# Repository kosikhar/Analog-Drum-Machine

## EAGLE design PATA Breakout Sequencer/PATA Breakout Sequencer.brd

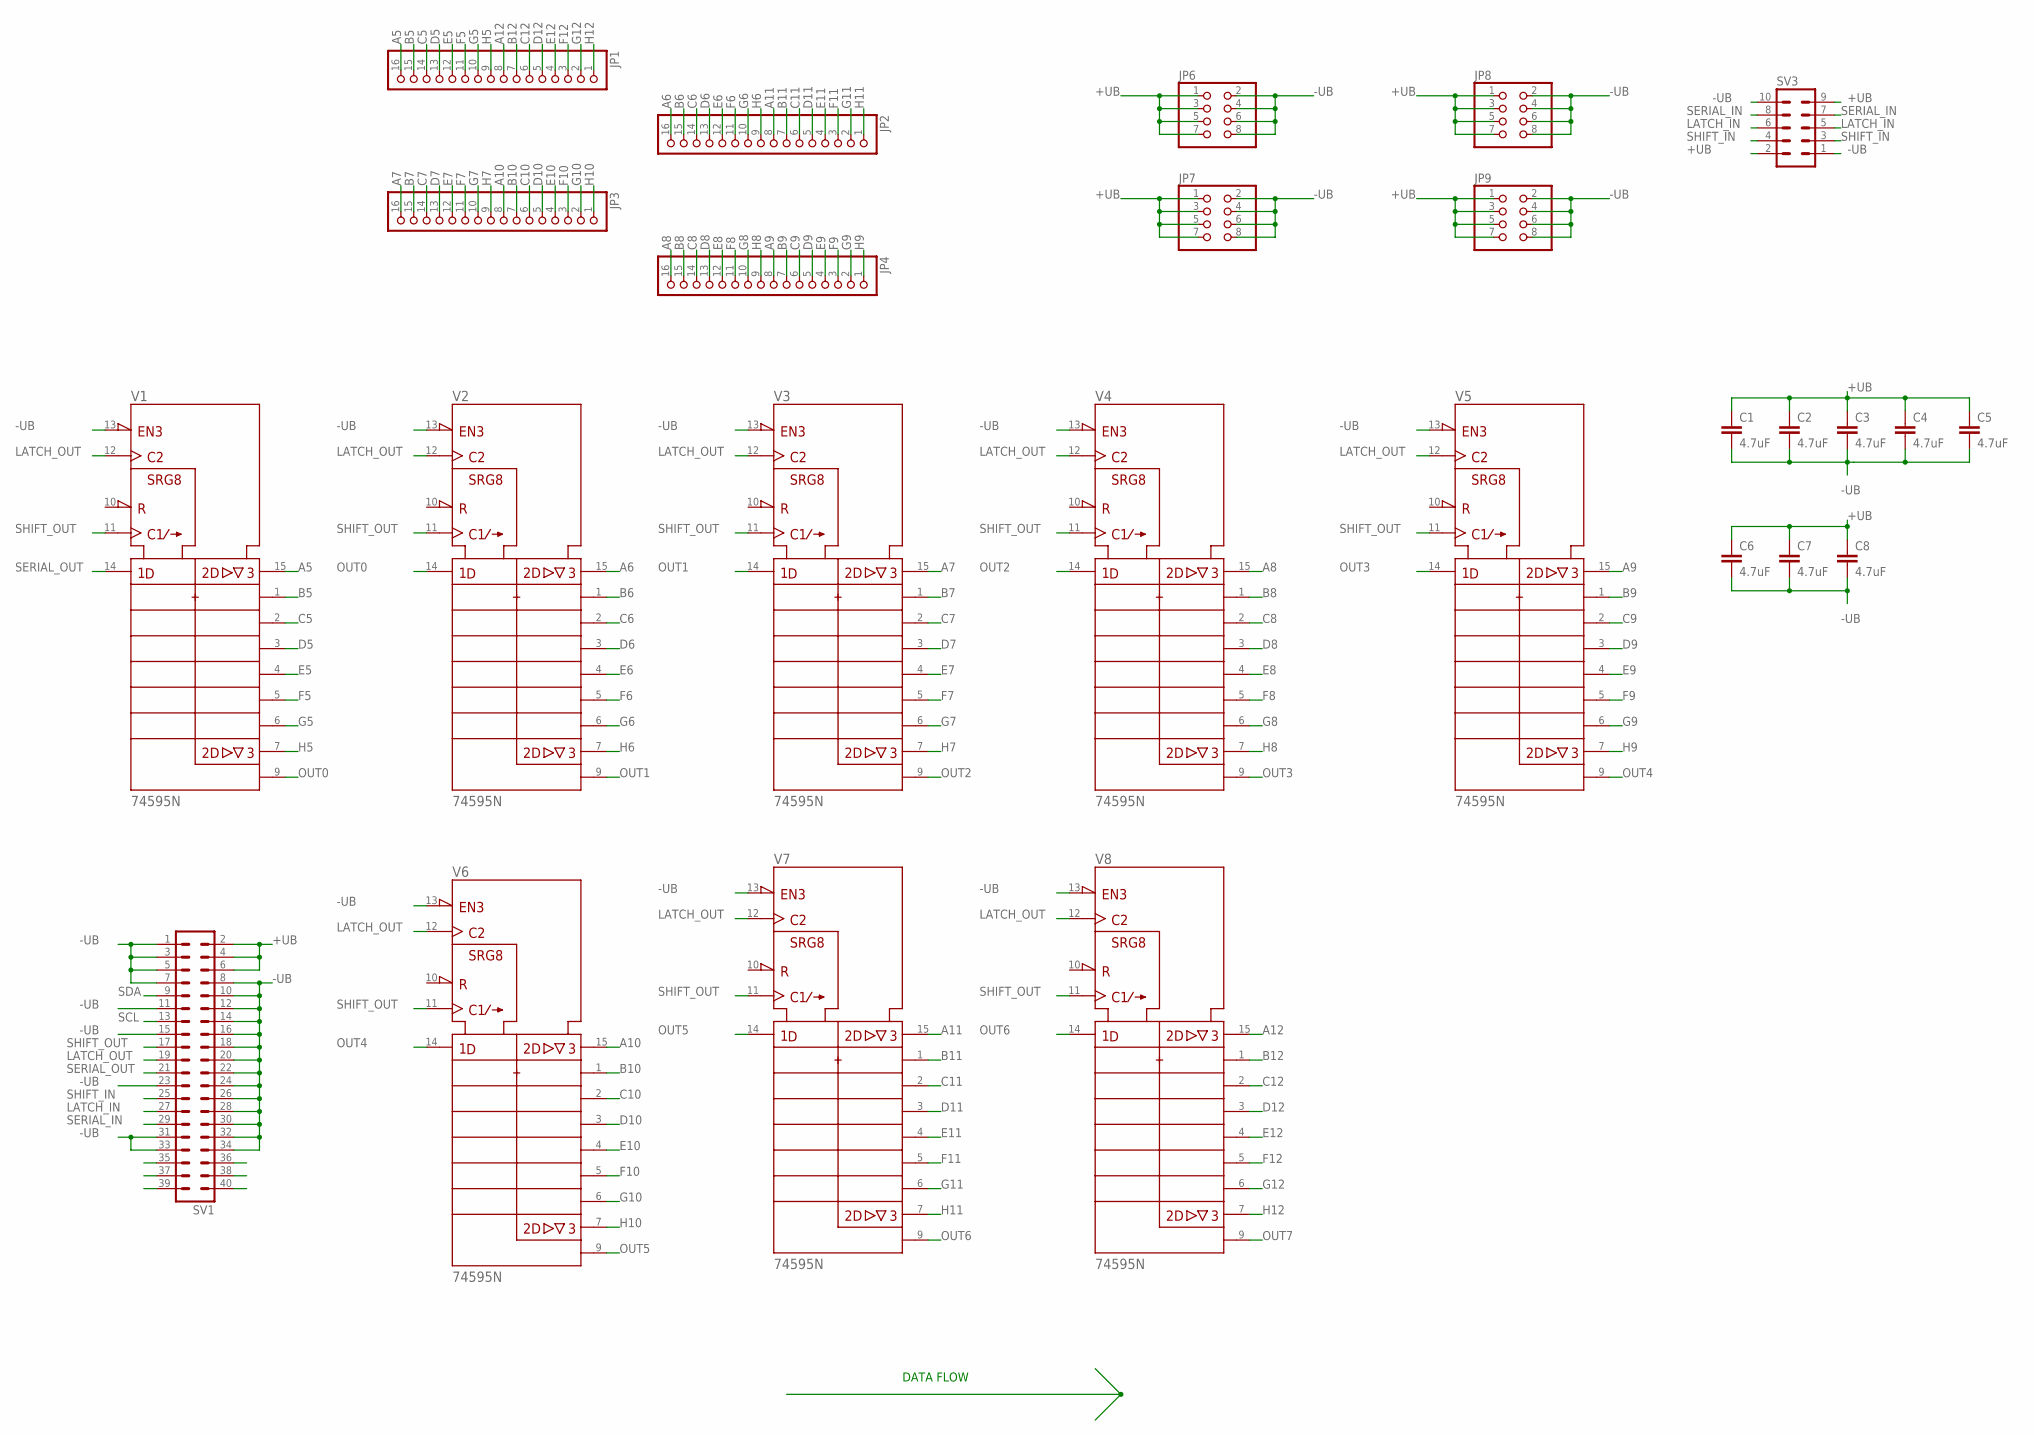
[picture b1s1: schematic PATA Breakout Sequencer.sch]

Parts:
C1, C2, C3, C4, C5, C6, C7, C8: 4.7uF; C050-024X044
JP1, JP2, JP3, JP4: PINHD-1X16; 1X16
JP6, JP7, JP8, JP9: PINHD-2X4; 2X04
SV1: MA20-2
SV3: MA05-2
V1, V2, V3, V4, V5, V6, V7, V8: 74595N; DIL16

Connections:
+UB: C1.1, C2.1, C3.1, C4.1, C5.1, C6.1, C7.1, C8.1, JP6.1, JP6.3, JP6.5, JP6.7, JP7.1, JP7.3, JP7.5, JP7.7, JP8.1, JP8.3, JP8.5, JP8.7, JP9.1, JP9.3, JP9.5, JP9.7, SV1.2, SV1.4, SV1.6, SV3.2, SV3.9, V1.16 (+UB), V2.16 (+UB), V3.16 (+UB), V4.16 (+UB), V5.16 (+UB), V6.16 (+UB), V7.16 (+UB), V8.16 (+UB)
-UB: C1.2, C2.2, C3.2, C4.2, C5.2, C6.2, C7.2, C8.2, JP6.2, JP6.4, JP6.6, JP6.8, JP7.2, JP7.4, JP7.6, JP7.8, JP8.2, JP8.4, JP8.6, JP8.8, JP9.2, JP9.4, JP9.6, JP9.8, SV1.1, SV1.3, SV1.5, SV1.7, SV1.8, SV1.10, SV1.11, SV1.12, SV1.14, SV1.15, SV1.16, SV1.18, SV1.20, SV1.22, SV1.23, SV1.24, SV1.26, SV1.28, SV1.30, SV1.31, SV1.32, SV1.33, SV1.34, SV3.1, SV3.10, V1.8 (-UB), V1.13 (!G), V2.8 (-UB), V2.13 (!G), V3.8 (-UB), V3.13 (!G), V4.8 (-UB), V4.13 (!G), V5.8 (-UB), V5.13 (!G), V6.8 (-UB), V6.13 (!G), V7.8 (-UB), V7.13 (!G), V8.8 (-UB), V8.13 (!G)
A5: JP1.16, V1.15 (QA)
A6: JP2.16, V2.15 (QA)
A7: JP3.16, V3.15 (QA)
A8: JP4.16, V4.15 (QA)
A9: JP4.8, V5.15 (QA)
A10: JP3.8, V6.15 (QA)
A11: JP2.8, V7.15 (QA)
A12: JP1.8, V8.15 (QA)
B5: JP1.15, V1.1 (QB)
B6: JP2.15, V2.1 (QB)
B7: JP3.15, V3.1 (QB)
B8: JP4.15, V4.1 (QB)
B9: JP4.7, V5.1 (QB)
B10: JP3.7, V6.1 (QB)
B11: JP2.7, V7.1 (QB)
B12: JP1.7, V8.1 (QB)
C5: JP1.14, V1.2 (QC)
C6: JP2.14, V2.2 (QC)
C7: JP3.14, V3.2 (QC)
C8: JP4.14, V4.2 (QC)
C9: JP4.6, V5.2 (QC)
C10: JP3.6, V6.2 (QC)
C11: JP2.6, V7.2 (QC)
C12: JP1.6, V8.2 (QC)
D5: JP1.13, V1.3 (QD)
D6: JP2.13, V2.3 (QD)
D7: JP3.13, V3.3 (QD)
D8: JP4.13, V4.3 (QD)
D9: JP4.5, V5.3 (QD)
D10: JP3.5, V6.3 (QD)
D11: JP2.5, V7.3 (QD)
D12: JP1.5, V8.3 (QD)
E5: JP1.12, V1.4 (QE)
E6: JP2.12, V2.4 (QE)
E7: JP3.12, V3.4 (QE)
E8: JP4.12, V4.4 (QE)
E9: JP4.4, V5.4 (QE)
E10: JP3.4, V6.4 (QE)
E11: JP2.4, V7.4 (QE)
E12: JP1.4, V8.4 (QE)
F5: JP1.11, V1.5 (QF)
F6: JP2.11, V2.5 (QF)
F7: JP3.11, V3.5 (QF)
F8: JP4.11, V4.5 (QF)
F9: JP4.3, V5.5 (QF)
F10: JP3.3, V6.5 (QF)
F11: JP2.3, V7.5 (QF)
F12: JP1.3, V8.5 (QF)
G5: JP1.10, V1.6 (QG)
G6: JP2.10, V2.6 (QG)
G7: JP3.10, V3.6 (QG)
G8: JP4.10, V4.6 (QG)
G9: JP4.2, V5.6 (QG)
G10: JP3.2, V6.6 (QG)
G11: JP2.2, V7.6 (QG)
G12: JP1.2, V8.6 (QG)
H5: JP1.9, V1.7 (QH)
H6: JP2.9, V2.7 (QH)
H7: JP3.9, V3.7 (QH)
H8: JP4.9, V4.7 (QH)
H9: JP4.1, V5.7 (QH)
H10: JP3.1, V6.7 (QH)
H11: JP2.1, V7.7 (QH)
H12: JP1.1, V8.7 (QH)
LATCH_IN: SV1.27, SV3.5, SV3.6
LATCH_OUT: SV1.19, V1.12 (RCK), V2.12 (RCK), V3.12 (RCK), V4.12 (RCK), V5.12 (RCK), V6.12 (RCK), V7.12 (RCK), V8.12 (RCK)
OUT0: V1.9 (QH*), V2.14 (SER)
OUT1: V2.9 (QH*), V3.14 (SER)
OUT2: V3.9 (QH*), V4.14 (SER)
OUT3: V4.9 (QH*), V5.14 (SER)
OUT4: V5.9 (QH*), V6.14 (SER)
OUT5: V6.9 (QH*), V7.14 (SER)
OUT6: V7.9 (QH*), V8.14 (SER)
OUT7: V8.9 (QH*)
SCL: SV1.13
SDA: SV1.9
SERIAL_IN: SV1.29, SV3.7, SV3.8
SERIAL_OUT: SV1.21, V1.14 (SER)
SHIFT_IN: SV1.25, SV3.3, SV3.4
SHIFT_OUT: SV1.17, V1.11 (SRCK), V2.11 (SRCK), V3.11 (SRCK), V4.11 (SRCK), V5.11 (SRCK), V6.11 (SRCK), V7.11 (SRCK), V8.11 (SRCK)

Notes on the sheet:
DATA FLOW

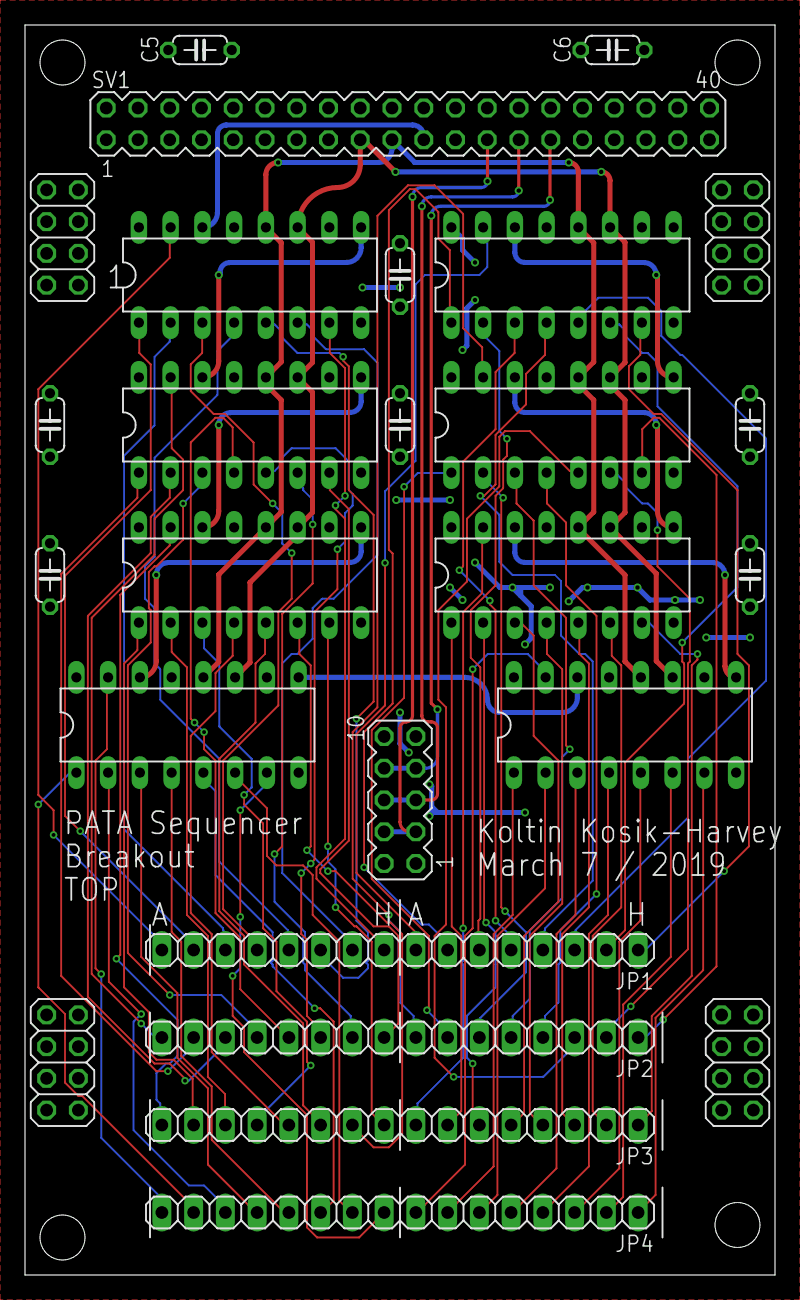
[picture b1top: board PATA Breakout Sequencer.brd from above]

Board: 2 copper layers, 60.0 x 100.0 mm, 26 parts (0 on the bottom side), 79 nets.

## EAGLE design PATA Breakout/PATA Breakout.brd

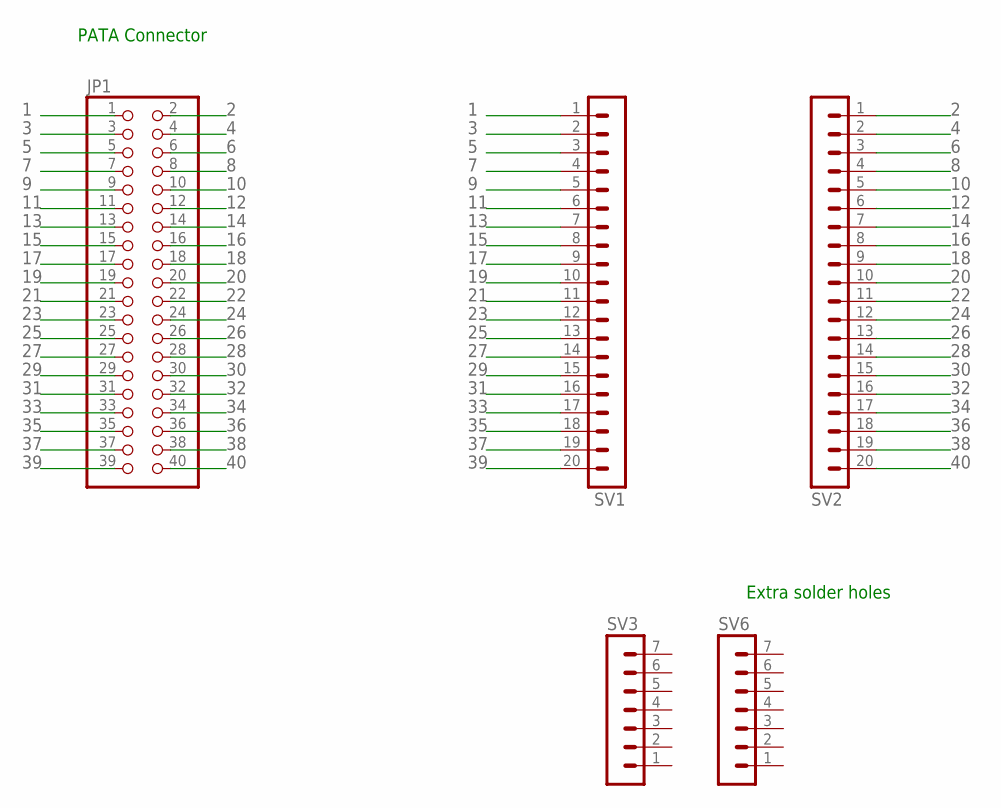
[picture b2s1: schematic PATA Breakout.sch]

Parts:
JP1: PINHD-2X20; 2X20
SV1, SV2: MA20-1L
SV3, SV6: MA07-1

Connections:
1: JP1.1, SV1.1
2: JP1.2, SV2.1
3: JP1.3, SV1.2
4: JP1.4, SV2.2
5: JP1.5, SV1.3
6: JP1.6, SV2.3
7: JP1.7, SV1.4
8: JP1.8, SV2.4
9: JP1.9, SV1.5
10: JP1.10, SV2.5
11: JP1.11, SV1.6
12: JP1.12, SV2.6
13: JP1.13, SV1.7
14: JP1.14, SV2.7
15: JP1.15, SV1.8
16: JP1.16, SV2.8
17: JP1.17, SV1.9
18: JP1.18, SV2.9
19: JP1.19, SV1.10
20: JP1.20, SV2.10
21: JP1.21, SV1.11
22: JP1.22, SV2.11
23: JP1.23, SV1.12
24: JP1.24, SV2.12
25: JP1.25, SV1.13
26: JP1.26, SV2.13
27: JP1.27, SV1.14
28: JP1.28, SV2.14
29: JP1.29, SV1.15
30: JP1.30, SV2.15
31: JP1.31, SV1.16
32: JP1.32, SV2.16
33: JP1.33, SV1.17
34: JP1.34, SV2.17
35: JP1.35, SV1.18
36: JP1.36, SV2.18
37: JP1.37, SV1.19
38: JP1.38, SV2.19
39: JP1.39, SV1.20
40: JP1.40, SV2.20

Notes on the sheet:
PATA Connector
Extra solder holes

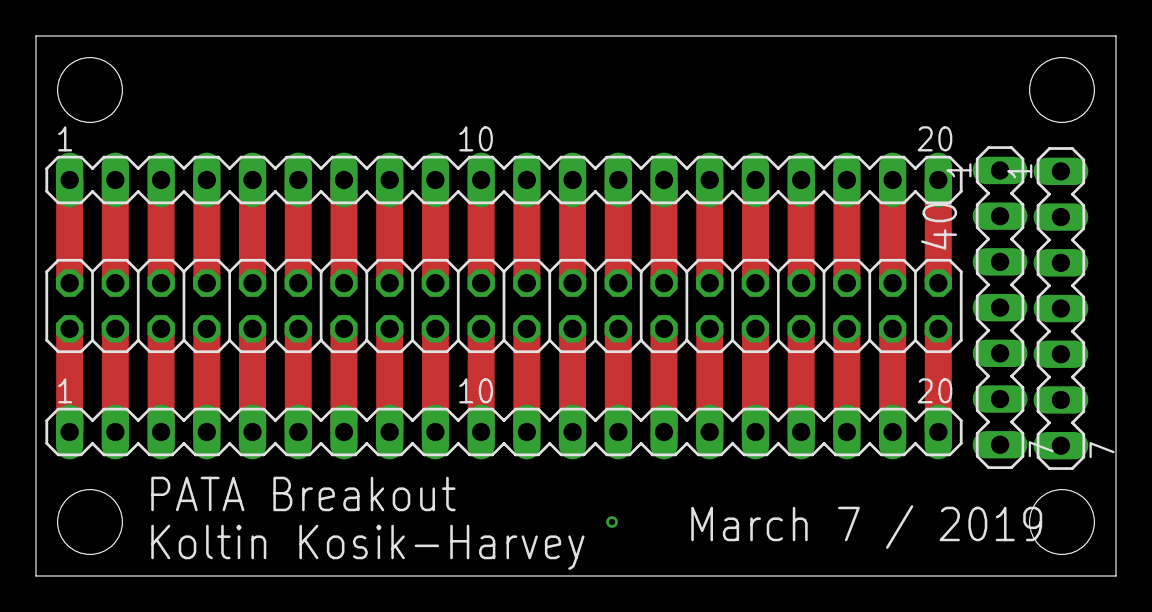
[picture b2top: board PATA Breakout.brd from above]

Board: 2 copper layers, 60.0 x 30.0 mm, 5 parts (0 on the bottom side), 40 nets.

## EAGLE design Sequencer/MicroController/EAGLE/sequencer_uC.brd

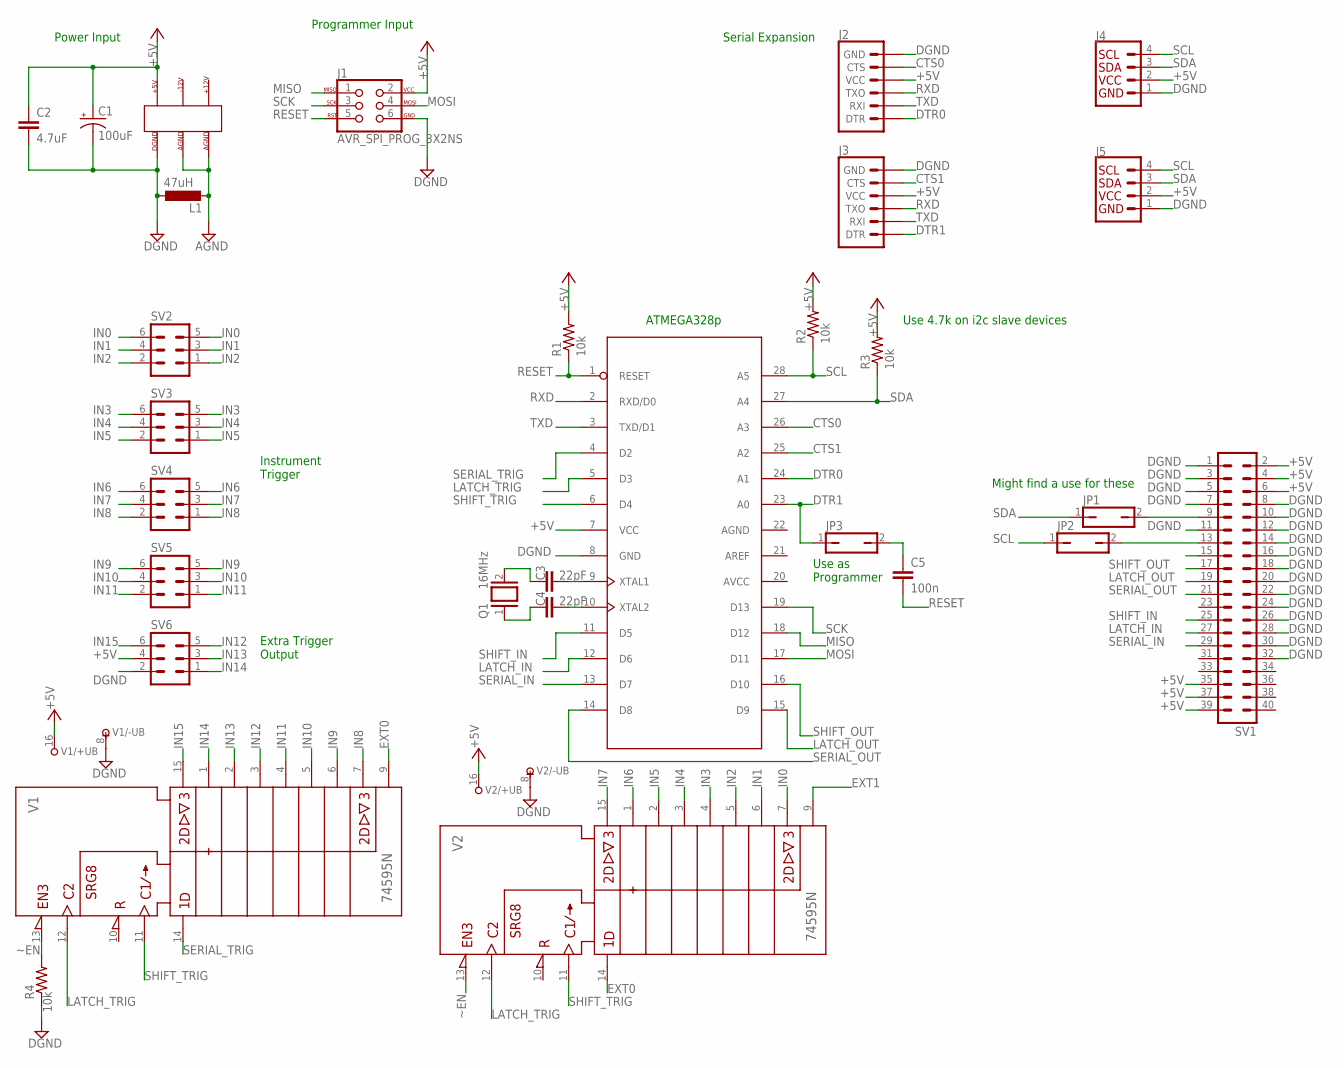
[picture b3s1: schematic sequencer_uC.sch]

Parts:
AT1: ATMEGA328; DIP28-0.3IN
C1: 100uF; E5-8,5
C2: 4.7uF; C050-024X044
C3, C4: 22pF; C050-024X044
C5: 100n; C050-024X044
J1: AVR_SPI_PROG_3X2NS; 2X3-NS
J2, J3: 6_PIN_SERIAL_TARGETLONGPADS; 1X06_LONGPADS
J4, J5: I2C_STANDARD; 1X04
JP1, JP2, JP3: JP1Q; JP1
L1: 47uH; 0207/10
Q1: 16MHz; QS
R1, R2, R3, R4: 10k; 0204/7
SV1: MA20-2
SV2, SV3, SV4, SV5, SV6: MA03-2
U$1: TER6PIN_VERT; CAPSTONE_1-770875-0
V1, V2: 74595N; DIL16

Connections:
+5V: AT1.7 (VCC), C1.+, C2.1, J1.2, J2.4 (VCC), J3.4 (VCC), J4.2, J5.2, R1.2, R2.2, R3.2, SV1.2, SV1.4, SV1.6, SV1.35, SV1.37, SV1.39, SV6.4, U$1.+5V, V1.16 (+UB), V2.16 (+UB)
AGND: L1.2, U$1.AGND0, U$1.AGND1
CTS0: AT1.26 (A3), J2.5 (CTS)
CTS1: AT1.25 (A2), J3.5 (CTS)
DGND: AT1.8 (GND), C1.-, C2.2, J1.6, J2.6 (GND), J3.6 (GND), J4.1, J5.1, L1.1, R4.1, SV1.1, SV1.3, SV1.5, SV1.7, SV1.8, SV1.10, SV1.11, SV1.12, SV1.14, SV1.15, SV1.16, SV1.18, SV1.20, SV1.22, SV1.24, SV1.26, SV1.28, SV1.30, SV1.32, SV6.2, U$1.DGND, U$1.NULL (DGND), V1.8 (-UB), V2.8 (-UB)
DTR0: AT1.24 (A1), J2.1 (DTR)
DTR1: AT1.23 (A0), J3.1 (DTR), JP3.1
EXT0: V1.9 (QH*), V2.14 (SER)
EXT1: V2.9 (QH*)
IN0: SV2.5, SV2.6, V2.7 (QH)
IN1: SV2.3, SV2.4, V2.6 (QG)
IN2: SV2.1, SV2.2, V2.5 (QF)
IN3: SV3.5, SV3.6, V2.4 (QE)
IN4: SV3.3, SV3.4, V2.3 (QD)
IN5: SV3.1, SV3.2, V2.2 (QC)
IN6: SV4.5, SV4.6, V2.1 (QB)
IN7: SV4.3, SV4.4, V2.15 (QA)
IN8: SV4.1, SV4.2, V1.7 (QH)
IN9: SV5.5, SV5.6, V1.6 (QG)
IN10: SV5.3, SV5.4, V1.5 (QF)
IN11: SV5.1, SV5.2, V1.4 (QE)
IN12: SV6.5, V1.3 (QD)
IN13: SV6.3, V1.2 (QC)
IN14: SV6.1, V1.1 (QB)
IN15: SV6.6, V1.15 (QA)
LATCH_IN: AT1.12 (D6), SV1.27
LATCH_OUT: AT1.15 (D9), SV1.19
LATCH_TRIG: AT1.5 (D3), V1.12 (RCK), V2.12 (RCK)
MISO: AT1.18 (D12), J1.1
MOSI: AT1.17 (D11), J1.4
unnamed: AT1.9 (XTAL1), C3.2
unnamed: AT1.10 (XTAL2), C4.2
unnamed: C3.1, Q1.2
unnamed: C4.1, Q1.1
unnamed: JP2.2, SV1.13
unnamed: JP1.2, SV1.9
unnamed: C5.1, JP3.2
RESET: AT1.1 (RESET), C5.2, J1.5, R1.1
RXD: AT1.2 (RXD/D0), J2.3 (TXO), J3.3 (TXO)
SCK: AT1.19 (D13), J1.3
SCL: AT1.28 (A5), J4.4, J5.4, JP2.1, R2.1
SDA: AT1.27 (A4), J4.3, J5.3, JP1.1, R3.1
SERIAL_IN: AT1.13 (D7), SV1.29
SERIAL_OUT: AT1.14 (D8), SV1.21
SERIAL_TRIG: AT1.4 (D2), V1.14 (SER)
SHIFT_IN: AT1.11 (D5), SV1.25
SHIFT_OUT: AT1.16 (D10), SV1.17
SHIFT_TRIG: AT1.6 (D4), V1.11 (SRCK), V2.11 (SRCK)
TXD: AT1.3 (TXD/D1), J2.2 (RXI), J3.2 (RXI)
~EN: R4.2, V1.13 (!G), V2.13 (!G)

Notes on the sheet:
ATMEGA328p
Serial Expansion
Power Input
Programmer Input
Instrument Trigger
Extra Trigger Output
Use 4.7k on i2c slave devices
Might find a use for these
Use as Programmer

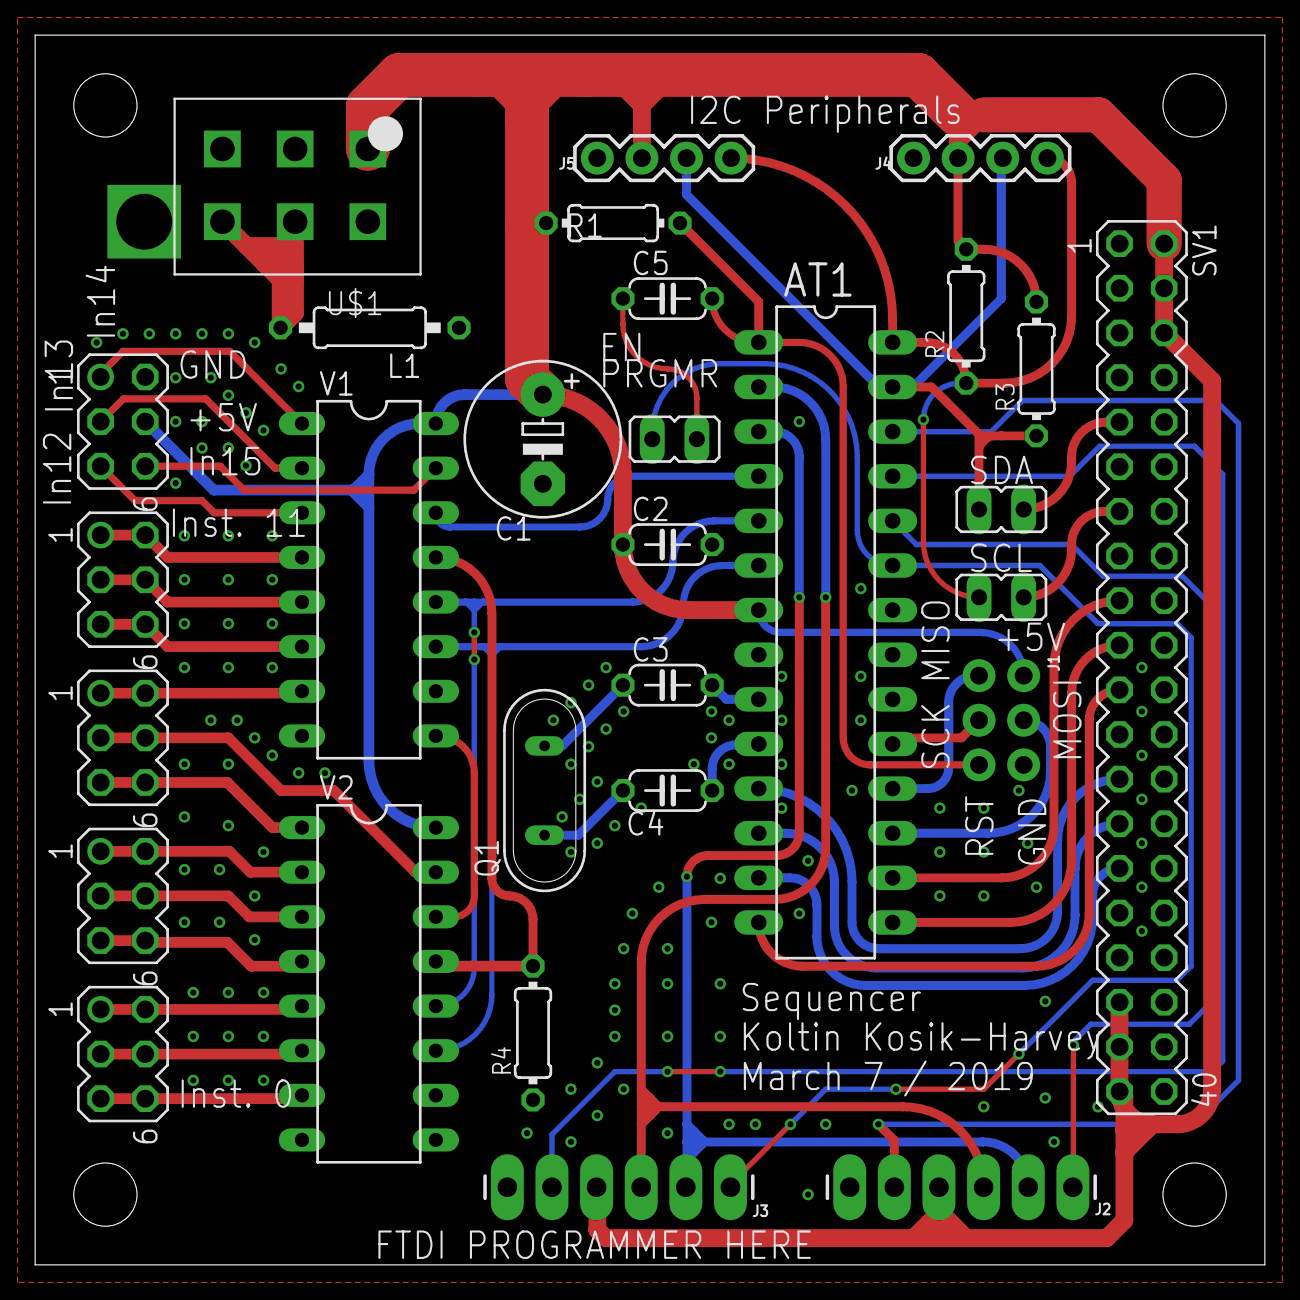
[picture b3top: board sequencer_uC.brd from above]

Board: 2 copper layers, 70.0 x 70.0 mm, 29 parts (0 on the bottom side), 49 nets.

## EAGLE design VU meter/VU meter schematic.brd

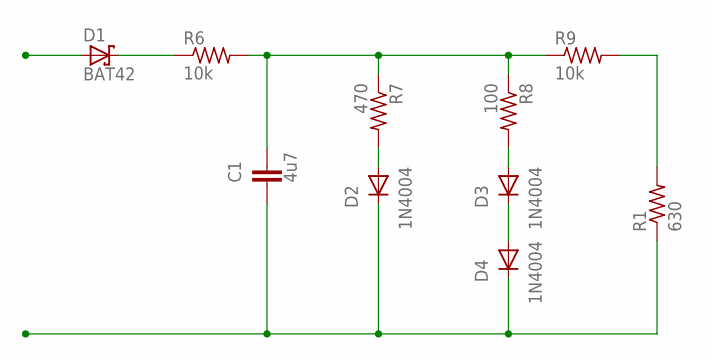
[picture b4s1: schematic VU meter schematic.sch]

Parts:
C1: 4u7; C2.5-3
D1: BAT42; DO35-10
D2, D3, D4: 1N4004; DO41-10
R1: 630; 0207/10
R6, R9: 10k; 0207/10
R7: 470; 0207/10
R8: 100; 0207/10

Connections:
unnamed: D1.C, R6.1
unnamed: C1.1, R6.2, R7.1, R8.1, R9.1
unnamed: C1.2, D2.C, D4.C, R1.1
unnamed: R1.2, R9.2
unnamed: D3.A, R8.2
unnamed: D3.C, D4.A
unnamed: D2.A, R7.2

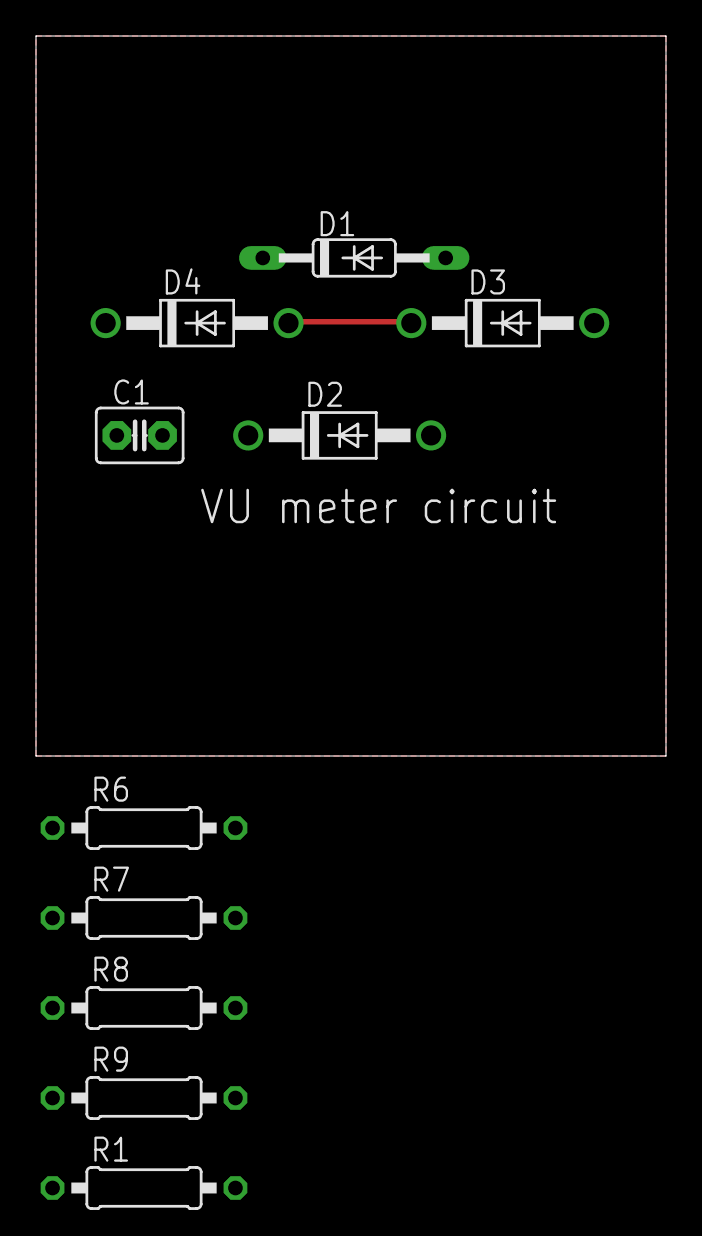
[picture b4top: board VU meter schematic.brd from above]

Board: 2 copper layers, 35.0 x 40.0 mm, 10 parts (0 on the bottom side), 7 nets.

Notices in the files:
parts and their libraries:
SparkFun-Connectors: Licensing: Creative Commons ShareAlike 4.0 International - https://creativecommons.org/licenses/by-sa/4.0
